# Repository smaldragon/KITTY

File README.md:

# KITTY Computer

the KITTY is a 65c02 homebrew kit microcomputer designed around text mode graphics and cartridge media. It is fully open source, and uses exclusively in-production parts. 

Quick Specs:

* **Bus Speed:** 3Mhz
* **CPU:*** w65c02s @~2.2Mhz (average)
* **RAM:** 28Kb SRAM
* **Video:** Custom, 256x256pixels, a text mode display using a preset font, 32x32 8x8 pixel characters, 16 color palette
* **Sound:** Custom, 8x1 Wavetable Audio, 3 melodic + 1 percussive channels, all with 4bit+4bit stereo volume control.
* **Input:** 40-Key Mechanical Keyboard
* **Media/Expansion:** 2 Cartridge Slots, each with up to 128x32Kb banks.
* **Interrupts:** /IRQ triggered when the video circuit has drawn the last visible pixels on the frame.
* **Output:** RGB PAL (50hz), via a SCART connector.

**[Computer Manual](https://smaldragon.github.io/KITTY)**

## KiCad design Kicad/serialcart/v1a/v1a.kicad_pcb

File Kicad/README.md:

# Kicad Files

**Note:** The files here are currently for wip versions of the board

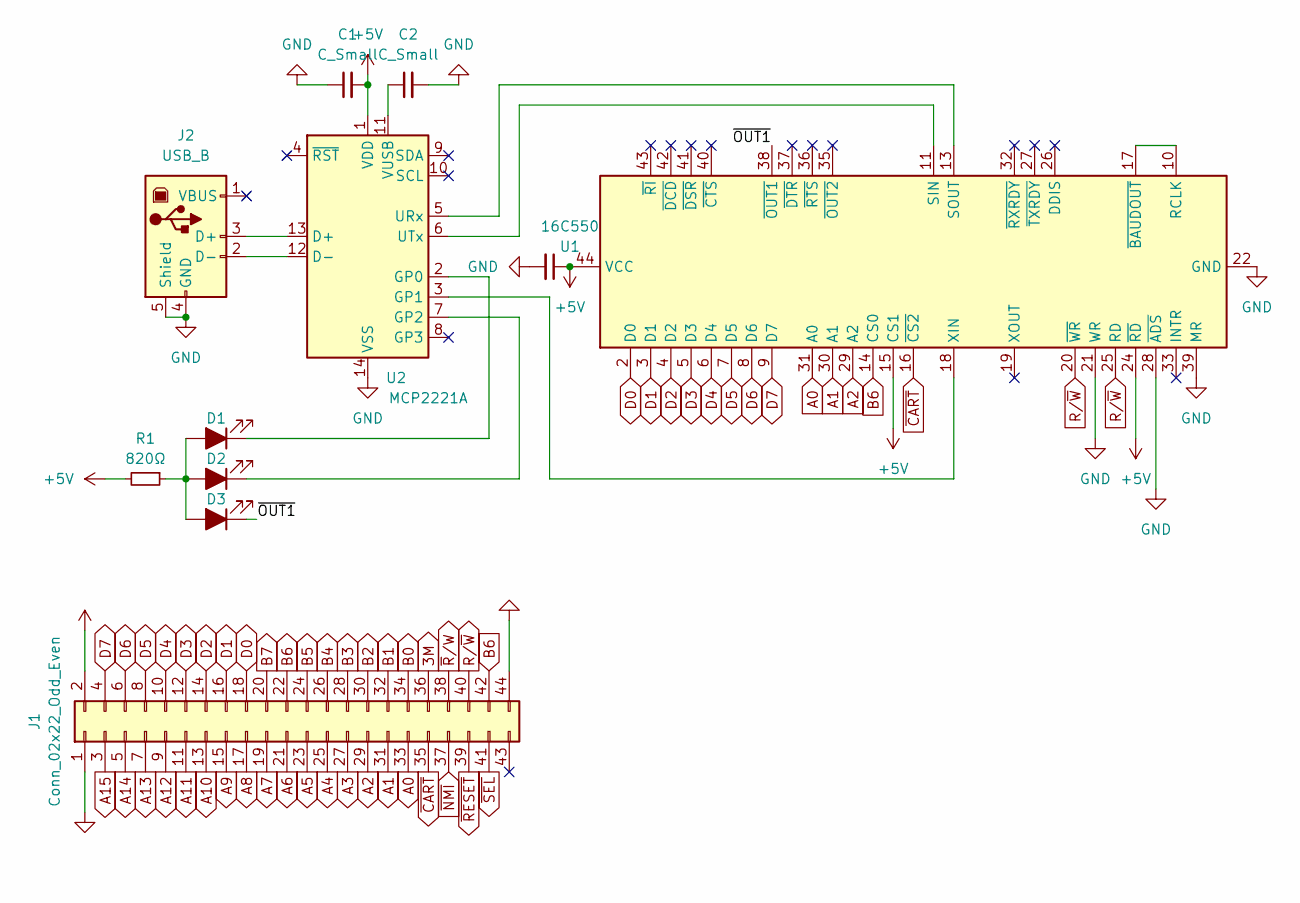
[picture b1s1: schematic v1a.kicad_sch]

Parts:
C1, C2, C3: C_Small; C_Disc_D3.0mm_W1.6mm_P2.50mm
D1, D2, D3: LED_Filled; LED_D3.0mm
J1: Conn_02x22_Odd_Even; KITTY_Cart_Edge
J2: USB_B; USB_B_OST_USB-B1HSxx_Horizontal
R1: 820Ω; R_Axial_DIN0204_L3.6mm_D1.6mm_P7.62mm_Horizontal
U1: 16C550; PLCC-44_THT-Socket
U2: MCP2221A; DIP-14_W7.62mm_Socket

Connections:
3M: J1.36
+5V: C1.2, C3.1, J1.2, R1.2, U1.15 (CS1), U1.24 (~RD), U1.44 (VCC), U2.1 (VDD)
/~OUT1: D3.1 (K), U1.38 (~OUT1)
A0: J1.33, U1.31 (A0)
A1: J1.31, U1.30 (A1)
A2: J1.29, U1.29 (A2)
A3: J1.27
A4: J1.25
A5: J1.23
A6: J1.21
A7: J1.19
A8: J1.17
A9: J1.15
A10: J1.13
A11: J1.11
A12: J1.9
A13: J1.7
A14: J1.5
A15: J1.3
B0: J1.34
B1: J1.32
B2: J1.30
B3: J1.28
B4: J1.26
B5: J1.24
B6: J1.22, J1.42, U1.14 (CS0)
B7: J1.20
D0: J1.18, U1.2 (D0)
D1: J1.16, U1.3 (D1)
D2: J1.14, U1.4 (D2)
D3: J1.12, U1.5 (D3)
D4: J1.10, U1.6 (D4)
D5: J1.8, U1.7 (D5)
D6: J1.6, U1.8 (D6)
D7: J1.4, U1.9 (D7)
GND: C1.1, C2.2, C3.2, J1.1, J1.44, J2.4 (GND), J2.5 (Shield), U1.21 (WR), U1.22 (GND), U1.28 (~ADS), U1.39 (MR), U2.14 (VSS)
unnamed: D1.2 (A), D2.2 (A), D3.2 (A), R1.1
unnamed: D1.1 (K), U2.2 (GP0)
unnamed: D2.1 (K), U2.7 (GP2)
unnamed: J2.3 (D+), U2.13 (D+)
unnamed: J2.2 (D-), U2.12 (D-)
unnamed: U1.10 (RCLK), U1.17 (~BAUDOUT)
unnamed: U1.11 (SIN), U2.6 (UTx)
unnamed: U1.13 (SOUT), U2.5 (URx)
unnamed: U1.18 (XIN), U2.3 (GP1)
unnamed: C2.1, U2.11 (VUSB)
R/~W: J1.40, U1.20 (~WR), U1.25 (RD)
~CART: J1.35, U1.16 (~CS2)
~NMI: J1.37
~RESET: J1.39
~R/W: J1.38
~SEL: J1.41

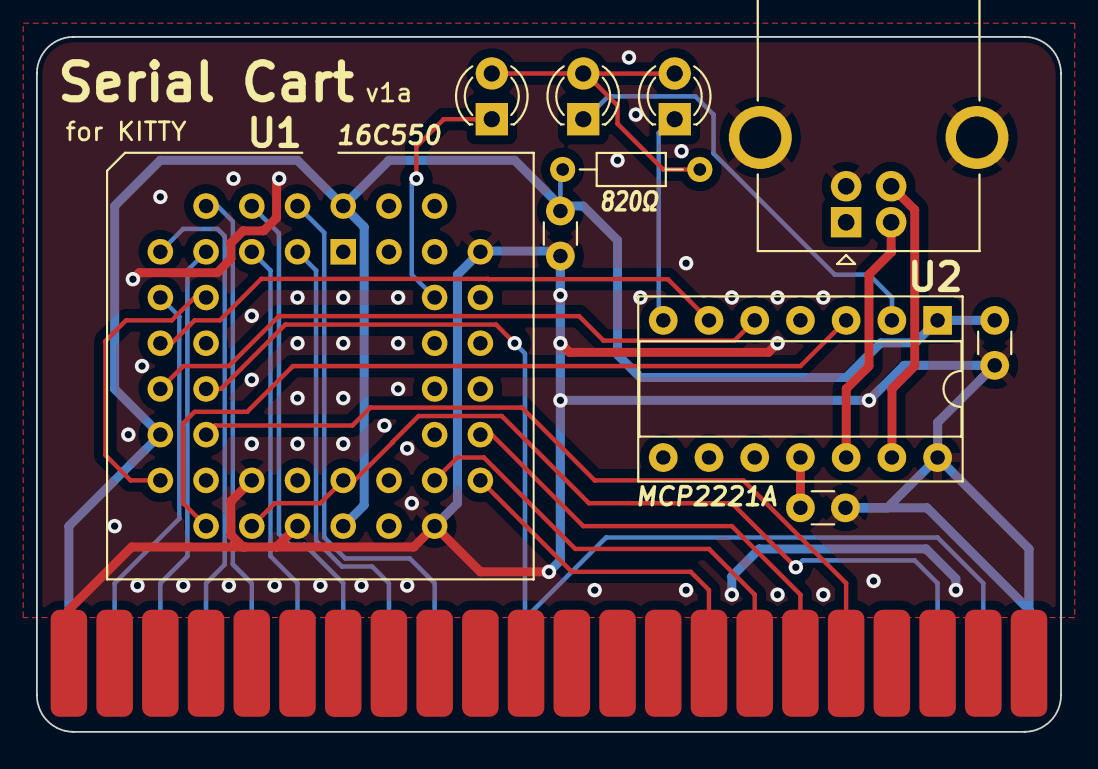
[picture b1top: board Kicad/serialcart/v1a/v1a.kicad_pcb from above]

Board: 2 copper layers, 56.9 x 38.6 mm, 11 parts (0 on the bottom side), 27 nets.

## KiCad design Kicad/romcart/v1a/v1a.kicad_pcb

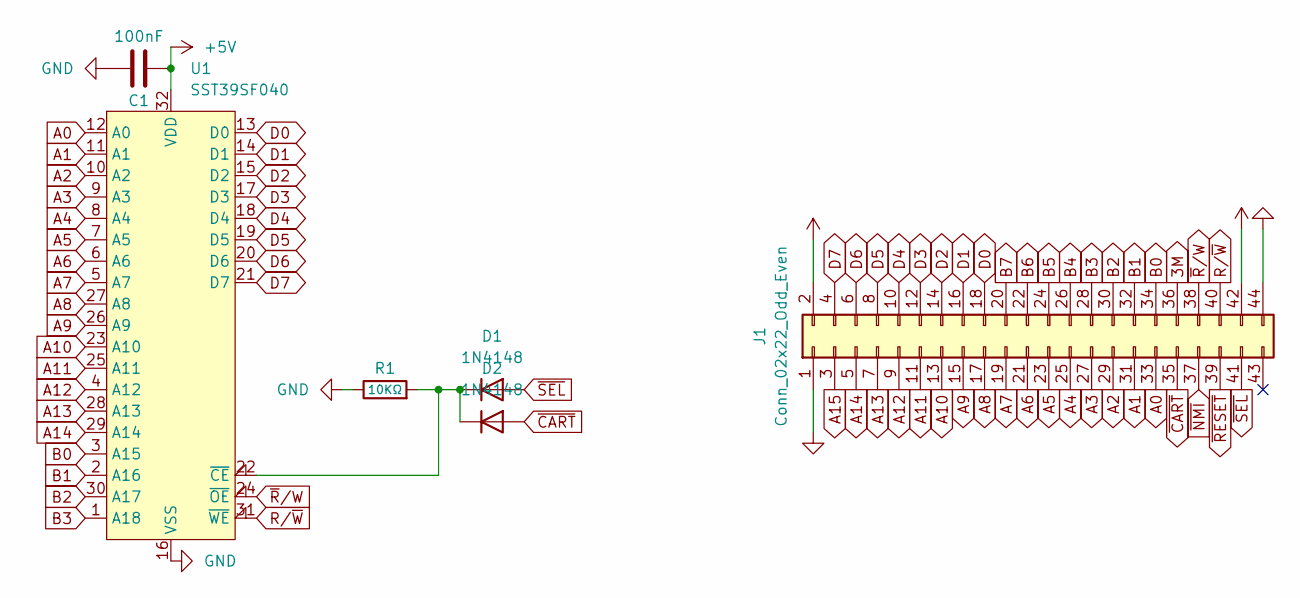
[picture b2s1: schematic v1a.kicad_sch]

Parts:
C1: 100nF; C_Disc_D3.0mm_W1.6mm_P2.50mm
D1, D2: 1N4148; D_DO-35_SOD27_P7.62mm_Horizontal
J1: Conn_02x22_Odd_Even; KITTY_Cart_Edge
R1: 10KΩ; R_Axial_DIN0204_L3.6mm_D1.6mm_P7.62mm_Horizontal
U1: SST39SF040; PLCC-32_THT-Socket

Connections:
3M: J1.36
+5V: C1.2, J1.2, J1.42, U1.32 (VDD)
A0: J1.33, U1.12 (A0)
A1: J1.31, U1.11 (A1)
A2: J1.29, U1.10 (A2)
A3: J1.27, U1.9 (A3)
A4: J1.25, U1.8 (A4)
A5: J1.23, U1.7 (A5)
A6: J1.21, U1.6 (A6)
A7: J1.19, U1.5 (A7)
A8: J1.17, U1.27 (A8)
A9: J1.15, U1.26 (A9)
A10: J1.13, U1.23 (A10)
A11: J1.11, U1.25 (A11)
A12: J1.9, U1.4 (A12)
A13: J1.7, U1.28 (A13)
A14: J1.5, U1.29 (A14)
A15: J1.3
B0: J1.34, U1.3 (A15)
B1: J1.32, U1.2 (A16)
B2: J1.30, U1.30 (A17)
B3: J1.28, U1.1 (A18)
B4: J1.26
B5: J1.24
B6: J1.22
B7: J1.20
D0: J1.18, U1.13 (D0)
D1: J1.16, U1.14 (D1)
D2: J1.14, U1.15 (D2)
D3: J1.12, U1.17 (D3)
D4: J1.10, U1.18 (D4)
D5: J1.8, U1.19 (D5)
D6: J1.6, U1.20 (D6)
D7: J1.4, U1.21 (D7)
GND: C1.1, J1.1, J1.44, R1.1, U1.16 (VSS)
unnamed: D1.1 (K), D2.1 (K), R1.2, U1.22 (~CE)
R/~W: J1.40, U1.31 (~WE)
~CART: D2.2 (A), J1.35
~NMI: J1.37
~RESET: J1.39
~R/W: J1.38, U1.24 (~OE)
~SEL: D1.2 (A), J1.41

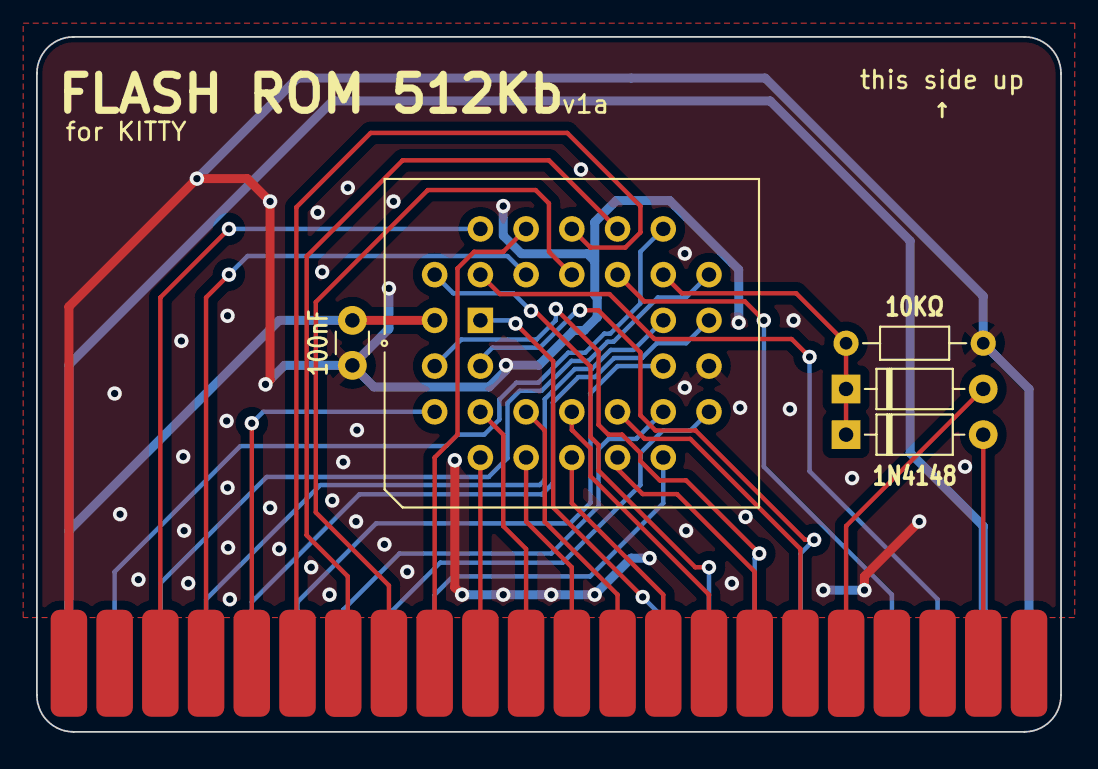
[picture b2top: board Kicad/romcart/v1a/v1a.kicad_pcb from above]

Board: 2 copper layers, 56.9 x 38.6 mm, 6 parts (0 on the bottom side), 34 nets.

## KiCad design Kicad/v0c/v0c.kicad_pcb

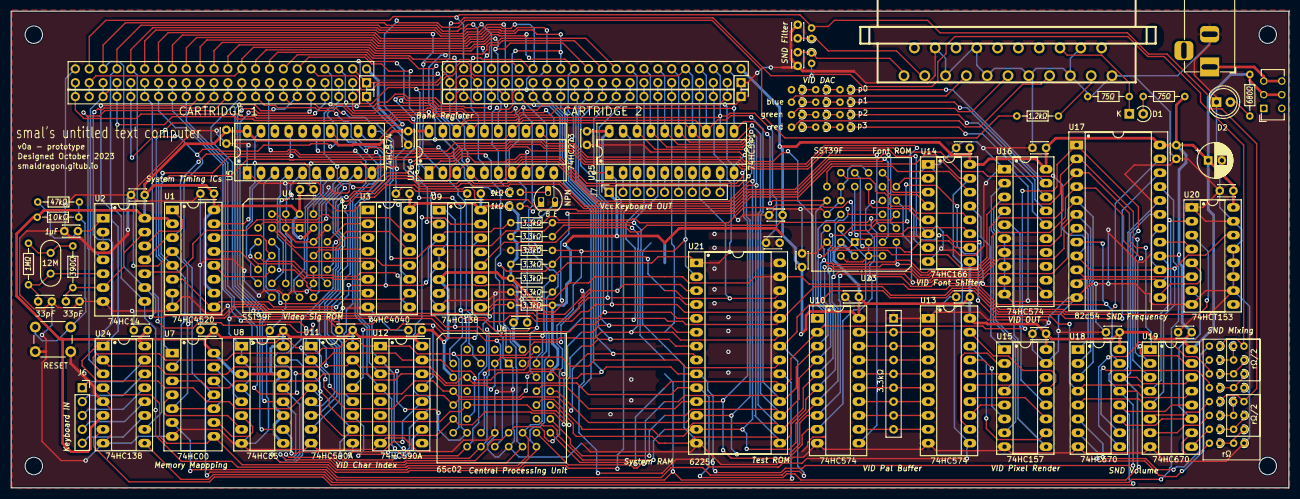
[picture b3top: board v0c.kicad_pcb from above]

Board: 2 copper layers, 234.0 x 87.3 mm, 123 parts (0 on the bottom side), 182 nets.

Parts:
C1: 1µF; C_Disc_D3.0mm_W2.0mm_P2.50mm
C2, C3: 33pF; C_Disc_D3.0mm_W2.0mm_P2.50mm
C4, C5, C6, C7, C8, C9, C10, C11, C12, C13, C14, C15, C16, C17, C18, C19, C20, C21, C22, C23, C24, C25, C26, C27, C28, C29, C31, C32: 100nF; C_Disc_D3.0mm_W2.0mm_P2.50mm
C30: C_Polarized; CP_Radial_D6.3mm_P2.50mm
D1: D_Small; D_A-405_P2.54mm_Vertical_KathodeUp
D2: Power; LED_D5.0mm
H1, H2, H3, H4: MountingHole; MountingHole_3.2mm_M3_ISO14580
J1: Barrel_Jack_MountingPin; BarrelJack_Horizontal
J2: SCART-F; SCART
J4, J8: Conn_02x22_Odd_Even; PinSocket_2x22_P2.54mm_Vertical
J5, J9: Conn_01x22; PinHeader_1x22_P2.54mm_Vertical
J6: Conn_01x05_Socket; PinSocket_1x05_P2.54mm_Vertical
J7: Conn_01x09_Socket; PinSocket_1x09_P2.54mm_Vertical
Q1: NPN; TO-92L_HandSolder
R1: 10kΩ; R_Axial_DIN0204_L3.6mm_D1.6mm_P7.62mm_Horizontal
R2: 1MΩ; R_Axial_DIN0204_L3.6mm_D1.6mm_P7.62mm_Horizontal
R3: 390Ω; R_Axial_DIN0204_L3.6mm_D1.6mm_P7.62mm_Horizontal
R4, R5, R7, R8, R10, R11, R14, R15, R18, R19: R2; R_Axial_DIN0204_L3.6mm_D1.6mm_P1.90mm_Vertical
R6, R9, R12, R13, R16, R17: R1; R_Axial_DIN0204_L3.6mm_D1.6mm_P1.90mm_Vertical
R20, R21, R22, R23, R24, R25, R29: 3.3kΩ; R_Axial_DIN0204_L3.6mm_D1.6mm_P7.62mm_Horizontal
R26, R28: 75Ω; R_Axial_DIN0204_L3.6mm_D1.6mm_P7.62mm_Horizontal
R27: 1.2kΩ; R_Axial_DIN0204_L3.6mm_D1.6mm_P7.62mm_Horizontal
R30, R31: 1kΩ; R_Axial_DIN0204_L3.6mm_D1.6mm_P1.90mm_Vertical
R32, R33, R34, R35, R36, R37, R38, R39, R40, R41, R42, R43, R46, R47: R_Small; R_Axial_DIN0204_L3.6mm_D1.6mm_P1.90mm_Vertical
R44: 680Ω; R_Axial_DIN0204_L3.6mm_D1.6mm_P7.62mm_Horizontal
R45: 47kΩ; R_Axial_DIN0204_L3.6mm_D1.6mm_P7.62mm_Horizontal
RN2: 3.3kΩ; R_Array_SIP9
SW1: SW_DPDT_x2; SW_CuK_JS202011AQN_DPDT_Angled
SW2: RESET; SW_PUSH_6mm
U1: 74HC4520; DIP-16_W7.62mm_Socket_LongPads
U2: 74HC14; DIP-14_W7.62mm_Socket_LongPads
U3: 74HC4040; DIP-16_W7.62mm_Socket_LongPads
U4, U23: SST39F; PLCC-32_THT-Socket
U5, U10, U13, U16: 74HC574; DIP-20_W7.62mm_Socket_LongPads
U6: 65c02; PLCC-44_THT-Socket
U7: 74HC00; DIP-14_W7.62mm_Socket_LongPads
U8: 74HC85; DIP-16_W7.62mm_Socket_LongPads
U9, U24: 74HC138; DIP-16_W7.62mm_Socket_LongPads
U11, U12: 74HC590A; DIP-16_W7.62mm_Socket_LongPads
U14: 74HC166; DIP-16_W7.62mm_Socket_LongPads
U15: 74HC157; DIP-16_W7.62mm_Socket_LongPads
U17: 82c54; DIP-24_W15.24mm_Socket_LongPads
U18, U19: 74HC670; DIP-16_W7.62mm_Socket_LongPads
U20: 74HCT153; DIP-16_W7.62mm_Socket_LongPads
U21: 62256; DIP-28_W15.24mm_Socket_LongPads
U25: 74HC541; DIP-20_W7.62mm_Socket_LongPads
U26: 74HC273; DIP-20_W7.62mm_Socket_LongPads
Y1: 12 Mhz; Crystal_HC52-8mm_Vertical

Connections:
1M: U1.5 (Q3), U7.2, U9.2 (A1), U17.9 (CLK0), U17.15 (CLK1), U17.18 (CLK2), U18.5 (Ra), U19.5 (Ra), U20.14 (S0)
3M: J4.36, J8.36, U1.4 (Q2), U6.41 (ϕ0), U7.5, U7.10, U7.12, U9.1 (A0)
6M: U1.3 (Q1), U2.11, U14.7 (Clk)
12M: U1.1 (CK), U2.12
750K: R20.2, U1.6 (Q4), U1.9 (CK), U5.11 (Cp), U9.3 (A2), U18.4 (Rb), U19.4 (Rb), U20.2 (S1)
+5V: C4.1, C5.1, C6.1, C7.1, C8.1, C9.1, C10.1, C11.1, C12.1, C13.1, C14.1, C15.1, C16.1, C17.1, C18.1, C19.1, C20.1, C21.1, C22.1, C23.1, C24.1, C25.1, C26.1, C27.1, C28.1, C29.1, C30.1, J4.2, J7.1, J8.2, R1.2, R21.2, R23.2, R24.2, R26.1, R29.2, R31.1, R44.1, SW1.2 (B), SW1.5 (B), U1.2 (Enable), U1.10 (Enable), U1.16 (VDD), U2.14 (VCC), U3.16 (VDD), U4.31 (~WE), U4.32 (VDD), U5.20 (VCC), U6.9 (VDD), U6.37 (VDD), U6.42 (~SO), U7.14 (VCC), U8.3 (Ia=b), U8.9 (B0), U8.11 (B1), U8.14 (B2), U8.16 (VCC), U9.6 (E2), U9.16 (VCC), U10.20 (VCC), U11.16 (VCC), U12.16 (VCC), U13.20 (VCC), U14.9 (Clr), U14.16 (VCC), U15.16 (VCC), U16.20 (VCC), U17.11 (G0), U17.14 (G1), U17.16 (G2), U17.24 (VCC), U18.16 (VCC), U19.16 (VCC), U20.16 (VCC), U21.28 (VCC), U23.31 (~WE), U23.32 (VDD), U24.6 (E2), U24.16 (VCC), U25.20 (VCC), U26.20 (VCC)
/Audio/L0: R5.2, U19.10 (Q1)
/Audio/L1: R10.2, U19.9 (Q2)
/Audio/L2: R14.2, U19.7 (Q3)
/Audio/L3: R18.2, U19.6 (Q4)
/Audio/Osc 1: U17.10 (OUT0), U20.6 (I0a)
/Audio/Osc 2: U17.13 (OUT1), U20.5 (I1a)
/Audio/Osc 3: U17.17 (OUT2), U20.4 (I2a)
/Audio/R0: R8.2, U18.10 (Q1)
/Audio/R1: R11.2, U18.9 (Q2)
/Audio/R2: R15.2, U18.7 (Q3)
/Audio/R3: R19.2, U18.6 (Q4)
/Audio/Sout: U18.11 (~Er), U19.11 (~Er), U20.7 (Za)
/IO/BANK: U24.10 (~Y5), U26.11 (Cp)
/IO/KeyIN 0: J6.1, U24.15 (~Y0)
/IO/KeyIN 1: J6.2, U24.14 (~Y1)
/IO/KeyIN 2: J6.3, U24.13 (~Y2)
/IO/KeyIN 3: J6.4, U24.12 (~Y3)
/IO/KeyIN 4: J6.5, U24.11 (~Y4)
/IO/KeyOUT 0: J7.2, U25.2 (A0)
/IO/KeyOUT 1: J7.3, U25.3 (A1)
/IO/KeyOUT 2: J7.4, U25.4 (A2)
/IO/KeyOUT 3: J7.5, U25.5 (A3)
/IO/KeyOUT 4: J7.6, U25.6 (A4)
/IO/KeyOUT 5: J7.7, U25.7 (A5)
/IO/KeyOUT 6: J7.8, U25.8 (A6)
/IO/KeyOUT 7: J7.9, U25.9 (A7)
/Ports/~B7: J8.41, J9.21, Q1.1 (C), R31.2
/Video/Pa0: U13.12 (Q7), U15.2 (I0a)
/Video/Pa1: U13.13 (Q6), U15.5 (I0b)
/Video/Pa2: U13.14 (Q5), U15.11 (I0c)
/Video/Pa3: U13.15 (Q4), U15.14 (I0d)
/Video/Pb0: U13.16 (Q3), U15.3 (I1a)
/Video/Pb1: U13.17 (Q2), U15.6 (I1b)
/Video/Pb2: U13.18 (Q1), U15.10 (I1c)
/Video/Pb3: U13.19 (Q0), U15.13 (I1d)
/Video/Y0: U11.5 (Q5), U23.8 (A4)
/Video/Y1: U11.6 (Q6), U23.7 (A5)
/Video/Y2: U11.7 (Q7), U23.6 (A6)
A0: J4.33, J5.17, J8.33, J9.17, U6.10 (A0), U11.15 (Q0), U17.19 (A0), U18.14 (Wa), U19.14 (Wa), U21.10 (A0)
A1: J4.31, J5.16, J8.31, J9.16, U6.11 (A1), U11.1 (Q1), U17.20 (A1), U18.13 (Wb), U19.13 (Wb), U21.9 (A1)
A2: J4.29, J5.15, J8.29, J9.15, U6.13 (A2), U11.2 (Q2), U21.8 (A2)
A3: J4.27, J5.14, J8.27, J9.14, U6.14 (A3), U11.3 (Q3), U21.7 (A3)
A4: J4.25, J5.13, J8.25, J9.13, U6.15 (A4), U11.4 (Q4), U21.6 (A4), U24.1 (A0)
A5: J4.23, J5.12, J8.23, J9.12, U6.16 (A5), U12.15 (Q0), U21.5 (A5), U24.2 (A1)
A6: J4.21, J5.11, J8.21, J9.11, U6.17 (A6), U12.1 (Q1), U21.4 (A6), U24.3 (A2)
A7: J4.19, J5.10, J8.19, J9.10, U6.18 (A7), U12.2 (Q2), U21.3 (A7), U25.1 (G1)
A8: J4.17, J5.9, J8.17, J9.9, U6.19 (A8), U12.3 (Q3), U21.25 (A8)
A9: J4.15, J5.8, J8.15, J9.8, U6.20 (A9), U12.4 (Q4), U20.3 (I3a), U21.24 (A9)
A10: J4.13, J5.7, J8.13, J9.7, R20.1, U6.21 (A10), U21.21 (A10)
A11: J4.11, J5.6, J8.11, J9.6, R21.1, U6.22 (A11), U21.23 (A11)
A12: J4.9, J5.5, J8.9, J9.5, R22.1, U6.25 (A12), U8.10 (A0), U21.2 (A12)
A13: J4.7, J5.4, J8.7, J9.4, R23.1, U6.26 (A13), U8.12 (A1), U21.26 (A13)
A14: J4.5, J5.3, J8.5, J9.3, R24.1, U6.27 (A14), U8.13 (A2), U21.1 (A14)
A15: J4.3, J5.2, J8.3, J9.2, R25.1, U6.28 (A15), U8.15 (A3)
B0: J4.34, J8.34, U26.2 (Q0)
B1: J4.32, J8.32, U26.5 (Q1)
B2: J4.30, J8.30, U26.6 (Q2)
B3: J4.28, J8.28, U26.9 (Q3)
B4: J4.26, J8.26, U26.12 (Q4)
B5: J4.24, J8.24, U26.15 (Q5)
B6: J4.22, J8.22, U26.16 (Q6)
B7: J4.20, J4.41, J5.21, J8.20, R30.1, U26.19 (Q7)
BusDriver: U6.3 (RDY), U6.40 (BE), U7.3, U11.14 (~OE), U12.14 (~OE)
D0: J4.18, J8.18, U6.36 (D0), U10.9 (D7), U17.8 (D0), U18.15 (D1), U21.11 (Q0), U23.12 (A0), U25.18 (Y0), U26.3 (D0)
D1: J4.16, J8.16, U6.35 (D1), U10.8 (D6), U17.7 (D1), U18.1 (D2), U21.12 (Q1), U23.11 (A1), U25.17 (Y1), U26.4 (D1)
D2: J4.14, J8.14, U6.34 (D2), U10.7 (D5), U17.6 (D2), U18.2 (D3), U21.13 (Q2), U23.10 (A2), U25.16 (Y2), U26.7 (D2)
D3: J4.12, J8.12, U6.33 (D3), U10.6 (D4), U17.5 (D3), U18.3 (D4), U21.15 (Q3), U23.9 (A3), U25.15 (Y3), U26.8 (D3)
D4: J4.10, J8.10, U6.32 (D4), U10.5 (D3), U17.4 (D4), U19.15 (D1), U21.16 (Q4), U23.5 (A7), U25.14 (Y4), U26.13 (D4)
D5: J4.8, J8.8, U6.31 (D5), U10.4 (D2), U17.3 (D5), U19.1 (D2), U21.17 (Q5), U23.27 (A8), U25.13 (Y5), U26.14 (D5)
D6: J4.6, J8.6, U6.30 (D6), U10.3 (D1), U17.2 (D6), U19.2 (D3), U21.18 (Q6), U23.26 (A9), U25.12 (Y6), U26.17 (D6)
D7: J4.4, J8.4, U6.29 (D7), U10.2 (D0), U17.1 (D7), U19.3 (D4), U21.19 (Q7), U23.23 (A10), U25.11 (Y7), U26.18 (D7)
GND: C1.1, C2.2, C3.2, C4.2, C5.2, C6.2, C7.2, C8.2, C9.2, C10.2, C11.2, C12.2, C13.2, C14.2, C15.2, C16.2, C17.2, C18.2, C19.2, C20.2, C21.2, C22.2, C23.2, C24.2, C25.2, C26.2, C27.2, C28.2, C29.2, C30.2, C31.1, C32.1, D2.1 (K), J1.2, J2.4, J2.5, J2.8, J2.9, J2.13, J2.17, J2.18, J2.21, J4.1, J4.44, J5.1, J8.1, J8.44, J9.1, Q1.3 (E), R4.1, R7.1, R22.2, R25.2, R28.2, RN2.1 (common), SW2.2, U1.7 (Reset), U1.8 (VSS), U2.7 (GND), U3.8 (VSS), U4.1 (A18), U4.2 (A16), U4.3 (A15), U4.16 (VSS), U4.22 (~CE), U4.24 (~OE), U4.28 (A13), U4.29 (A14), U4.30 (A17), U5.1 (OE), U5.10 (GND), U6.1 (VSS), U6.23 (VSS), U6.24 (VSS), U7.7 (GND), U8.1 (B3), U8.2 (Ia<b), U8.4 (Ia>b), U8.8 (GND), U9.4 (~E0), U9.5 (~E1), U9.8 (GND), U10.10 (GND), U11.8 (GND), U12.8 (GND), U13.1 (OE), U13.10 (GND), U14.1 (Ds), U14.6 (CE), U14.8 (GND), U15.8 (GND), U15.15 (E), U16.1 (OE), U16.6 (D4), U16.7 (D5), U16.8 (D6), U16.9 (D7), U16.10 (GND), U17.12 (GND), U18.8 (GND), U19.8 (GND), U20.1 (Ea), U20.8 (GND), U20.10 (I0b), U20.11 (I1b), U20.12 (I2b), U20.13 (I3b), U20.15 (Eb), U21.14 (GND), U21.22 (~OE), U23.1 (A18), U23.2 (A16), U23.3 (A15), U23.4 (A12), U23.16 (VSS), U23.22 (~CE), U23.24 (~OE), U23.25 (A11), U23.28 (A13), U23.29 (A14), U23.30 (A17), U24.5 (~E1), U24.8 (GND), U25.10 (GND), U26.10 (GND)
LEFT: J4.42, J8.42, R16.2, R18.1, R46.2
unnamed: C1.2, R45.1, U2.1
unnamed: C2.1, R2.1, U2.5, Y1.1
unnamed: C3.1, R3.1, U2.6, U2.13
unnamed: D1.2 (A), R26.2
unnamed: D1.1 (K), J2.16, R28.1
unnamed: D2.2 (A), R44.2
unnamed: C31.2, J2.1, R47.1
unnamed: C32.2, J2.3, R46.1
unnamed: J2.19, R27.2
unnamed: Q1.2 (B), R30.2
unnamed: R1.1, R45.2, SW2.1
unnamed: R2.2, R3.2, Y1.2
unnamed: R4.2, R5.1, R6.1
unnamed: R7.2, R8.1, R9.1
unnamed: R6.2, R10.1, R12.1
unnamed: R9.2, R11.1, R13.1
unnamed: R12.2, R14.1, R16.1
unnamed: R13.2, R15.1, R17.1
unnamed: R32.2, R36.1
unnamed: R33.2, R37.1
unnamed: R34.2, R38.1
unnamed: R35.2, R39.1
unnamed: R36.2, R40.1
unnamed: R37.2, R41.1
unnamed: R38.2, R42.1
unnamed: R39.2, R43.1
unnamed: RN2.2 (R1), U10.19 (Q0), U13.2 (D0)
unnamed: RN2.3 (R2), U10.18 (Q1), U13.3 (D1)
unnamed: RN2.4 (R3), U10.17 (Q2), U13.4 (D2)
unnamed: RN2.5 (R4), U10.16 (Q3), U13.5 (D3)
unnamed: RN2.6 (R5), U10.15 (Q4), U13.6 (D4)
unnamed: RN2.7 (R6), U10.14 (Q5), U13.7 (D5)
unnamed: RN2.8 (R7), U10.13 (Q6), U13.8 (D6)
unnamed: RN2.9 (R8), U10.12 (Q7), U13.9 (D7)
unnamed: U1.12 (Q2), U4.12 (A0)
unnamed: U1.13 (Q3), U4.11 (A1)
unnamed: U1.14 (Q4), U3.10 (CLK), U4.10 (A2)
unnamed: U3.9 (Q0), U4.9 (A3)
unnamed: U3.7 (Q1), U4.8 (A4)
unnamed: U3.6 (Q2), U4.7 (A5)
unnamed: U3.5 (Q3), U4.6 (A6)
unnamed: U3.3 (Q4), U4.5 (A7)
unnamed: U3.2 (Q5), U4.27 (A8)
unnamed: U3.4 (Q6), U4.26 (A9)
unnamed: U3.13 (Q7), U4.23 (A10)
unnamed: U3.12 (Q8), U4.25 (A11)
unnamed: U3.14 (Q9), U4.4 (A12)
unnamed: U4.13 (D0), U5.2 (D0)
unnamed: U4.14 (D1), U5.3 (D1)
unnamed: U4.15 (D2), U5.4 (D2)
unnamed: U4.17 (D3), U5.5 (D3)
unnamed: U4.18 (D4), U5.6 (D4)
unnamed: U4.19 (D5), U5.7 (D5)
unnamed: U4.20 (D6), U5.8 (D6)
unnamed: U4.21 (D7), U5.9 (D7)
unnamed: U7.4, U8.7 (Oa<b)
unnamed: U7.9, U8.6 (Oa=b)
unnamed: U7.13, U8.5 (Oa>b)
unnamed: U11.9 (~RCO), U12.12 (~CE)
unnamed: U14.2 (A), U23.13 (D0)
unnamed: U14.3 (B), U23.14 (D1)
unnamed: U14.4 (C), U23.15 (D2)
unnamed: U14.5 (D), U23.17 (D3)
unnamed: U14.10 (E), U23.18 (D4)
unnamed: U14.11 (F), U23.19 (D5)
unnamed: U14.12 (G), U23.20 (D6)
unnamed: U14.14 (H), U23.21 (D7)
unnamed: U14.13 (Qh), U15.1 (S)
unnamed: U15.4 (Za), U16.2 (D0)
unnamed: U15.7 (Zb), U16.3 (D1)
unnamed: U15.9 (Zc), U16.4 (D2)
unnamed: U15.12 (Zd), U16.5 (D3)
unnamed: R32.1, U16.19 (Q0)
unnamed: R33.1, U16.18 (Q1)
unnamed: R34.1, U16.17 (Q2)
unnamed: R35.1, U16.16 (Q3)
RESET: U2.2, U2.3
RIGHT: J4.43, J5.22, J8.43, J9.22, R17.2, R19.1, R47.2
R/~W: J4.40, J8.40, U2.9, U6.38 (R/~W), U17.23 (~WR), U21.27 (~WE)
VBUS: J1.1, SW1.3 (C), SW1.6 (C)
VBlue: J2.7, R41.2
VGreen: J2.11, R42.2
VPixel: U5.17 (Q2), U7.1
VRed: J2.15, R43.2
VReset: U1.15 (Reset), U3.11 (Reset), U5.19 (Q0)
~6M: U2.10, U16.11 (Cp)
~CART: J4.35, J5.18, J8.35, J9.18, U7.11
~CharTickReg: U9.14 (~Y1), U11.13 (CPR), U12.13 (CPR)
~CharTick: U9.15 (~Y0), U11.11 (CPC), U12.11 (CPC)
~ChrGet: U9.7 (~Y7), U14.15 (PE)
~IO: U7.8, U24.4 (~E0), U25.19 (G2)
~NMI: J4.37, J5.19, J8.37, J9.19, R29.1, U6.7 (~NMI)
~OscWr: U17.21 (~CS), U24.9 (~Y6)
~PalGet: U9.12 (~Y3), U10.11 (Cp)
~PalPush: U9.9 (~Y6), U13.11 (Cp)
~RAM: U7.6, U21.20 (~CS)
~RESET: J4.39, J5.20, J8.39, J9.20, U2.4, U6.44 (~RES), U26.1 (~Mr)
~R/W: J4.38, J8.38, U2.8, U17.22 (~RD)
~VIrq: U5.12 (Q7), U6.5 (~IRQ)
~VPixel: U5.13 (Q6), U10.1 (OE), U11.12 (~CE)
~VReset: U5.15 (Q4), U11.10 (~MRC), U12.10 (~MRC)
~VSync: R27.1, U5.14 (Q5)
~VolWr: U18.12 (~Ew), U19.12 (~Ew), U24.7 (~Y7)

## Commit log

2023-10-20 add assembly.md
2023-10-20 add bom.md
2023-10-21 guide more
2023-11-02 Update README.md
    keys
2023-11-09 various files
2023-11-09 fix schematics
2023-11-13 fix frequency addresses in README.md
2023-12-13 Add wip docs and v1a kicad files
2023-12-13 update docs
2023-12-13 spelling
2023-12-14 v1a update
2023-12-15 Add video DAC to documentation
2024-01-05 Add documentation regarding cartridge pinout
2024-01-05 Add files relating to v1a and v1b revisions
2024-01-12 Video ROM update, cart files, v1b main board
